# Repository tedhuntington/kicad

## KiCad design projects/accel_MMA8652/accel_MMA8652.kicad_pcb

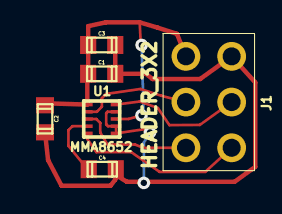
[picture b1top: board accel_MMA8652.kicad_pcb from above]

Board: 2 copper layers, 6 parts (0 on the bottom side), 7 nets.

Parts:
C1: 1uF; TED_SM0603
C2, C3, C4: .1uF; TED_SM0603
J1: HEADER_3X2; TED_HEADER_3x2_BOTTOM
U1: MMA8652; TED_DFN-10

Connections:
+2.8v: C1.1, C2.1, C3.1, J1.1, U1.1, U1.8
GND: C1.2, C2.2, C3.2, C4.2, J1.6, U1.6, U1.7, U1.9
INT1: J1.3, U1.3
INT2: J1.4, U1.5
unnamed: C4.1, U1.4
SCL: J1.2, U1.2
SDA: J1.5, U1.10

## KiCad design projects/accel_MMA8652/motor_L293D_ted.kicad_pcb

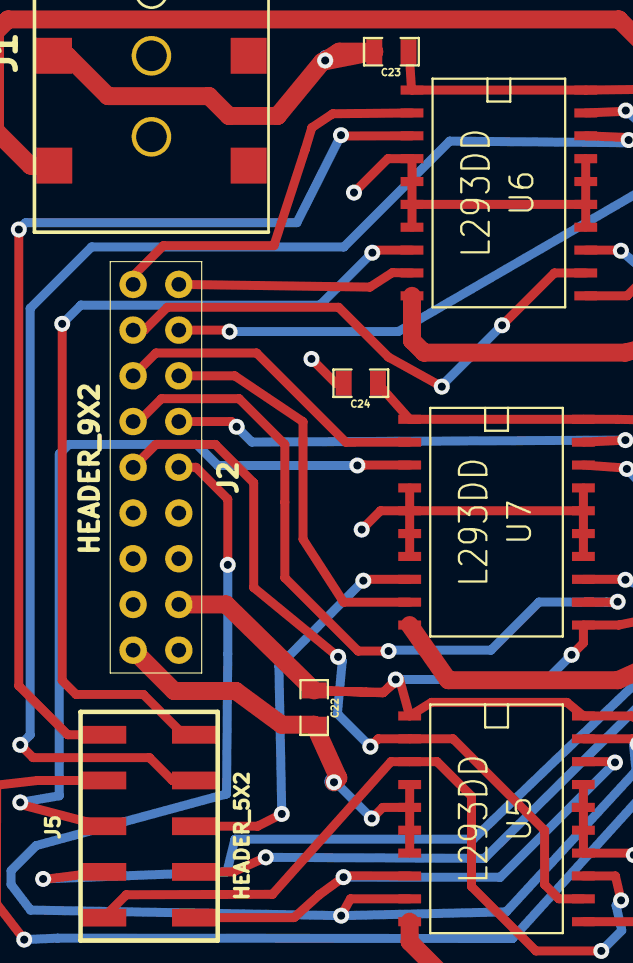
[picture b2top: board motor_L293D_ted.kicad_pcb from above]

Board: 2 copper layers, 9 parts (0 on the bottom side), 23 nets.

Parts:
C22, C23, C24: .1uF; TED_SM0805
J1: Motor DC_2.1MM; TED_DC_2.1mm_SMT
J2: HEADER_9X2; TED_HEADER_9x2_TOP
J5: HEADER_5X2; TED_HEADER_5x2_SMT
U5, U6, U7: L293DD; SO20

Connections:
+5v_Vbus: C22.1, C23.1, C24.1, J2.11, U5.1, U5.11, U5.20, U6.1, U6.11, U6.20, U7.1, U7.11, U7.20
GND: C22.2, C23.2, C24.2, J1.2, J2.9, U5.4, U5.5, U5.6, U5.7, U5.14, U5.15, U5.16, U5.17, U6.4, U6.5, U6.6, U6.7, U6.14, U6.15, U6.16, U6.17, U7.4, U7.5, U7.6, U7.7, U7.14, U7.15, U7.16, U7.17
ICSPCLK_M1-: J2.18, U6.9
ICSPDAT_M1+: J2.1, U6.2
M2+: J2.2, U6.12
M2-: J2.17, U6.19
M3+: J2.3, U7.2
M3-: J2.16, U7.9
M4+: J2.4, U7.12
M4-: J2.15, U7.19
M5+: J2.5, U5.2, U5.12
M5-: J2.14, U5.9, U5.19
Motor1+: J5.1, U6.3
Motor1-: J5.10, U6.8
Motor2+: J5.2, U6.13
Motor2-: J5.9, U6.18
Motor3+: J5.3, U7.3
Motor3-: J5.8, U7.8
Motor4+: J5.4, U7.13
Motor4-: J5.7, U7.18
Motor5+: J5.5, U5.3, U5.13
Motor5-: J5.6, U5.8, U5.18
Vin: J1.1, U5.10, U6.10, U7.10

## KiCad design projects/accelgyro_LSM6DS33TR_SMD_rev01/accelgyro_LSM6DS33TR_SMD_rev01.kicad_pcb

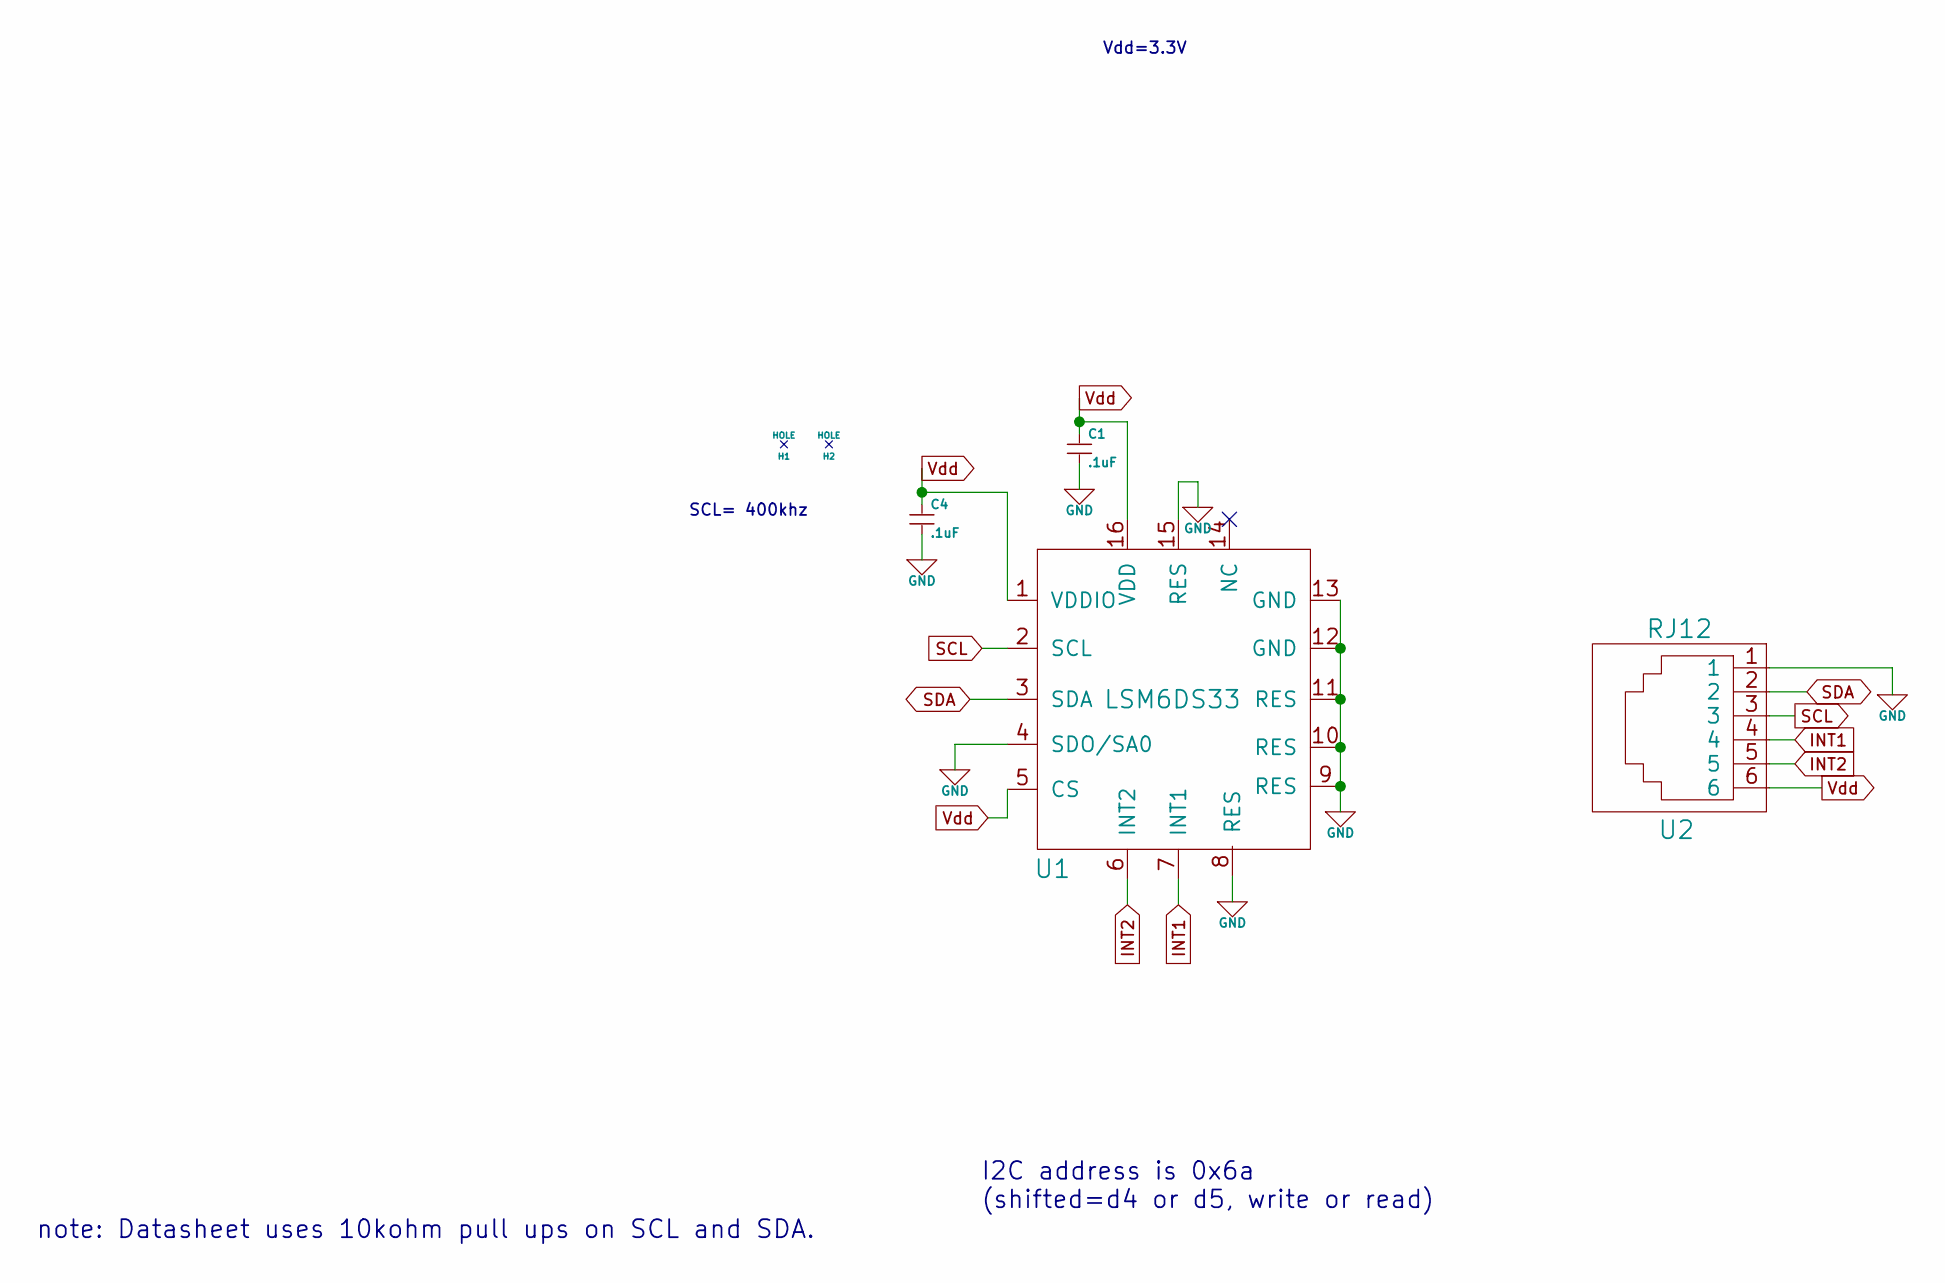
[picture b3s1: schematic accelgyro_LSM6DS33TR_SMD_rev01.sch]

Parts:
C1, C4: .1uF; TED_SM0603_C
H1, H2: HOLE; TED_Hole_3mm
U1: LSM6DS33; LGA-16
U2: RJ12; TED_RJ12_855135002

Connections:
GND: C1.2, C4.2, U1.4 (SDO/SA0), U1.8 (RES), U1.9 (RES), U1.10 (RES), U1.11 (RES), U1.12 (GND), U1.13 (GND), U1.15 (RES), U2.1
INT1: U1.7 (INT1), U2.4
INT2: U1.6 (INT2), U2.5
SCL: U1.2 (SCL), U2.3
SDA: U1.3 (SDA), U2.2
Vdd: C1.1, C4.1, U1.1 (VDDIO), U1.5 (CS), U1.16 (VDD), U2.6

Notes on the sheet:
Vdd=3.3V
I2C address is 0x6a (shifted=d4 or d5, write or read)
SCL= 400khz
note: Datasheet uses 10kohm pull ups on SCL and SDA.

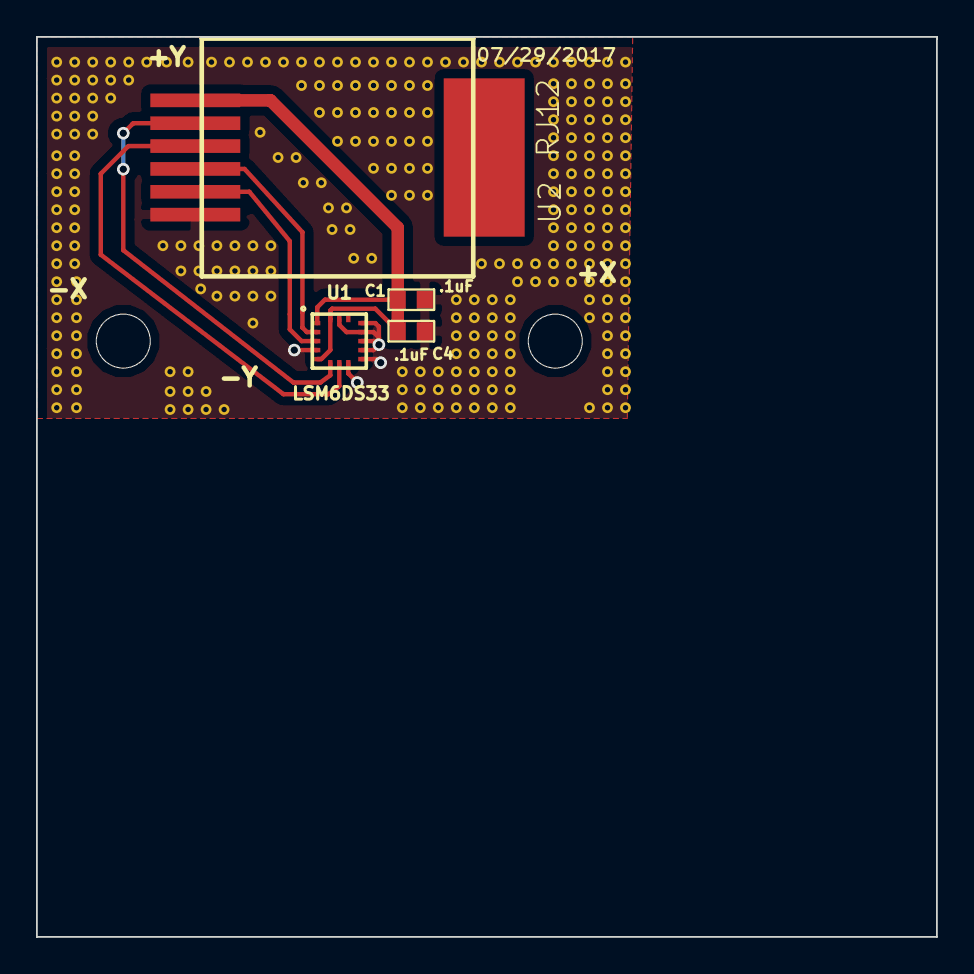
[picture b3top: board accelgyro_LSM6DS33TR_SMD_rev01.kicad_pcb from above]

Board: 2 copper layers, 50.0 x 50.0 mm, 6 parts (0 on the bottom side), 6 nets.

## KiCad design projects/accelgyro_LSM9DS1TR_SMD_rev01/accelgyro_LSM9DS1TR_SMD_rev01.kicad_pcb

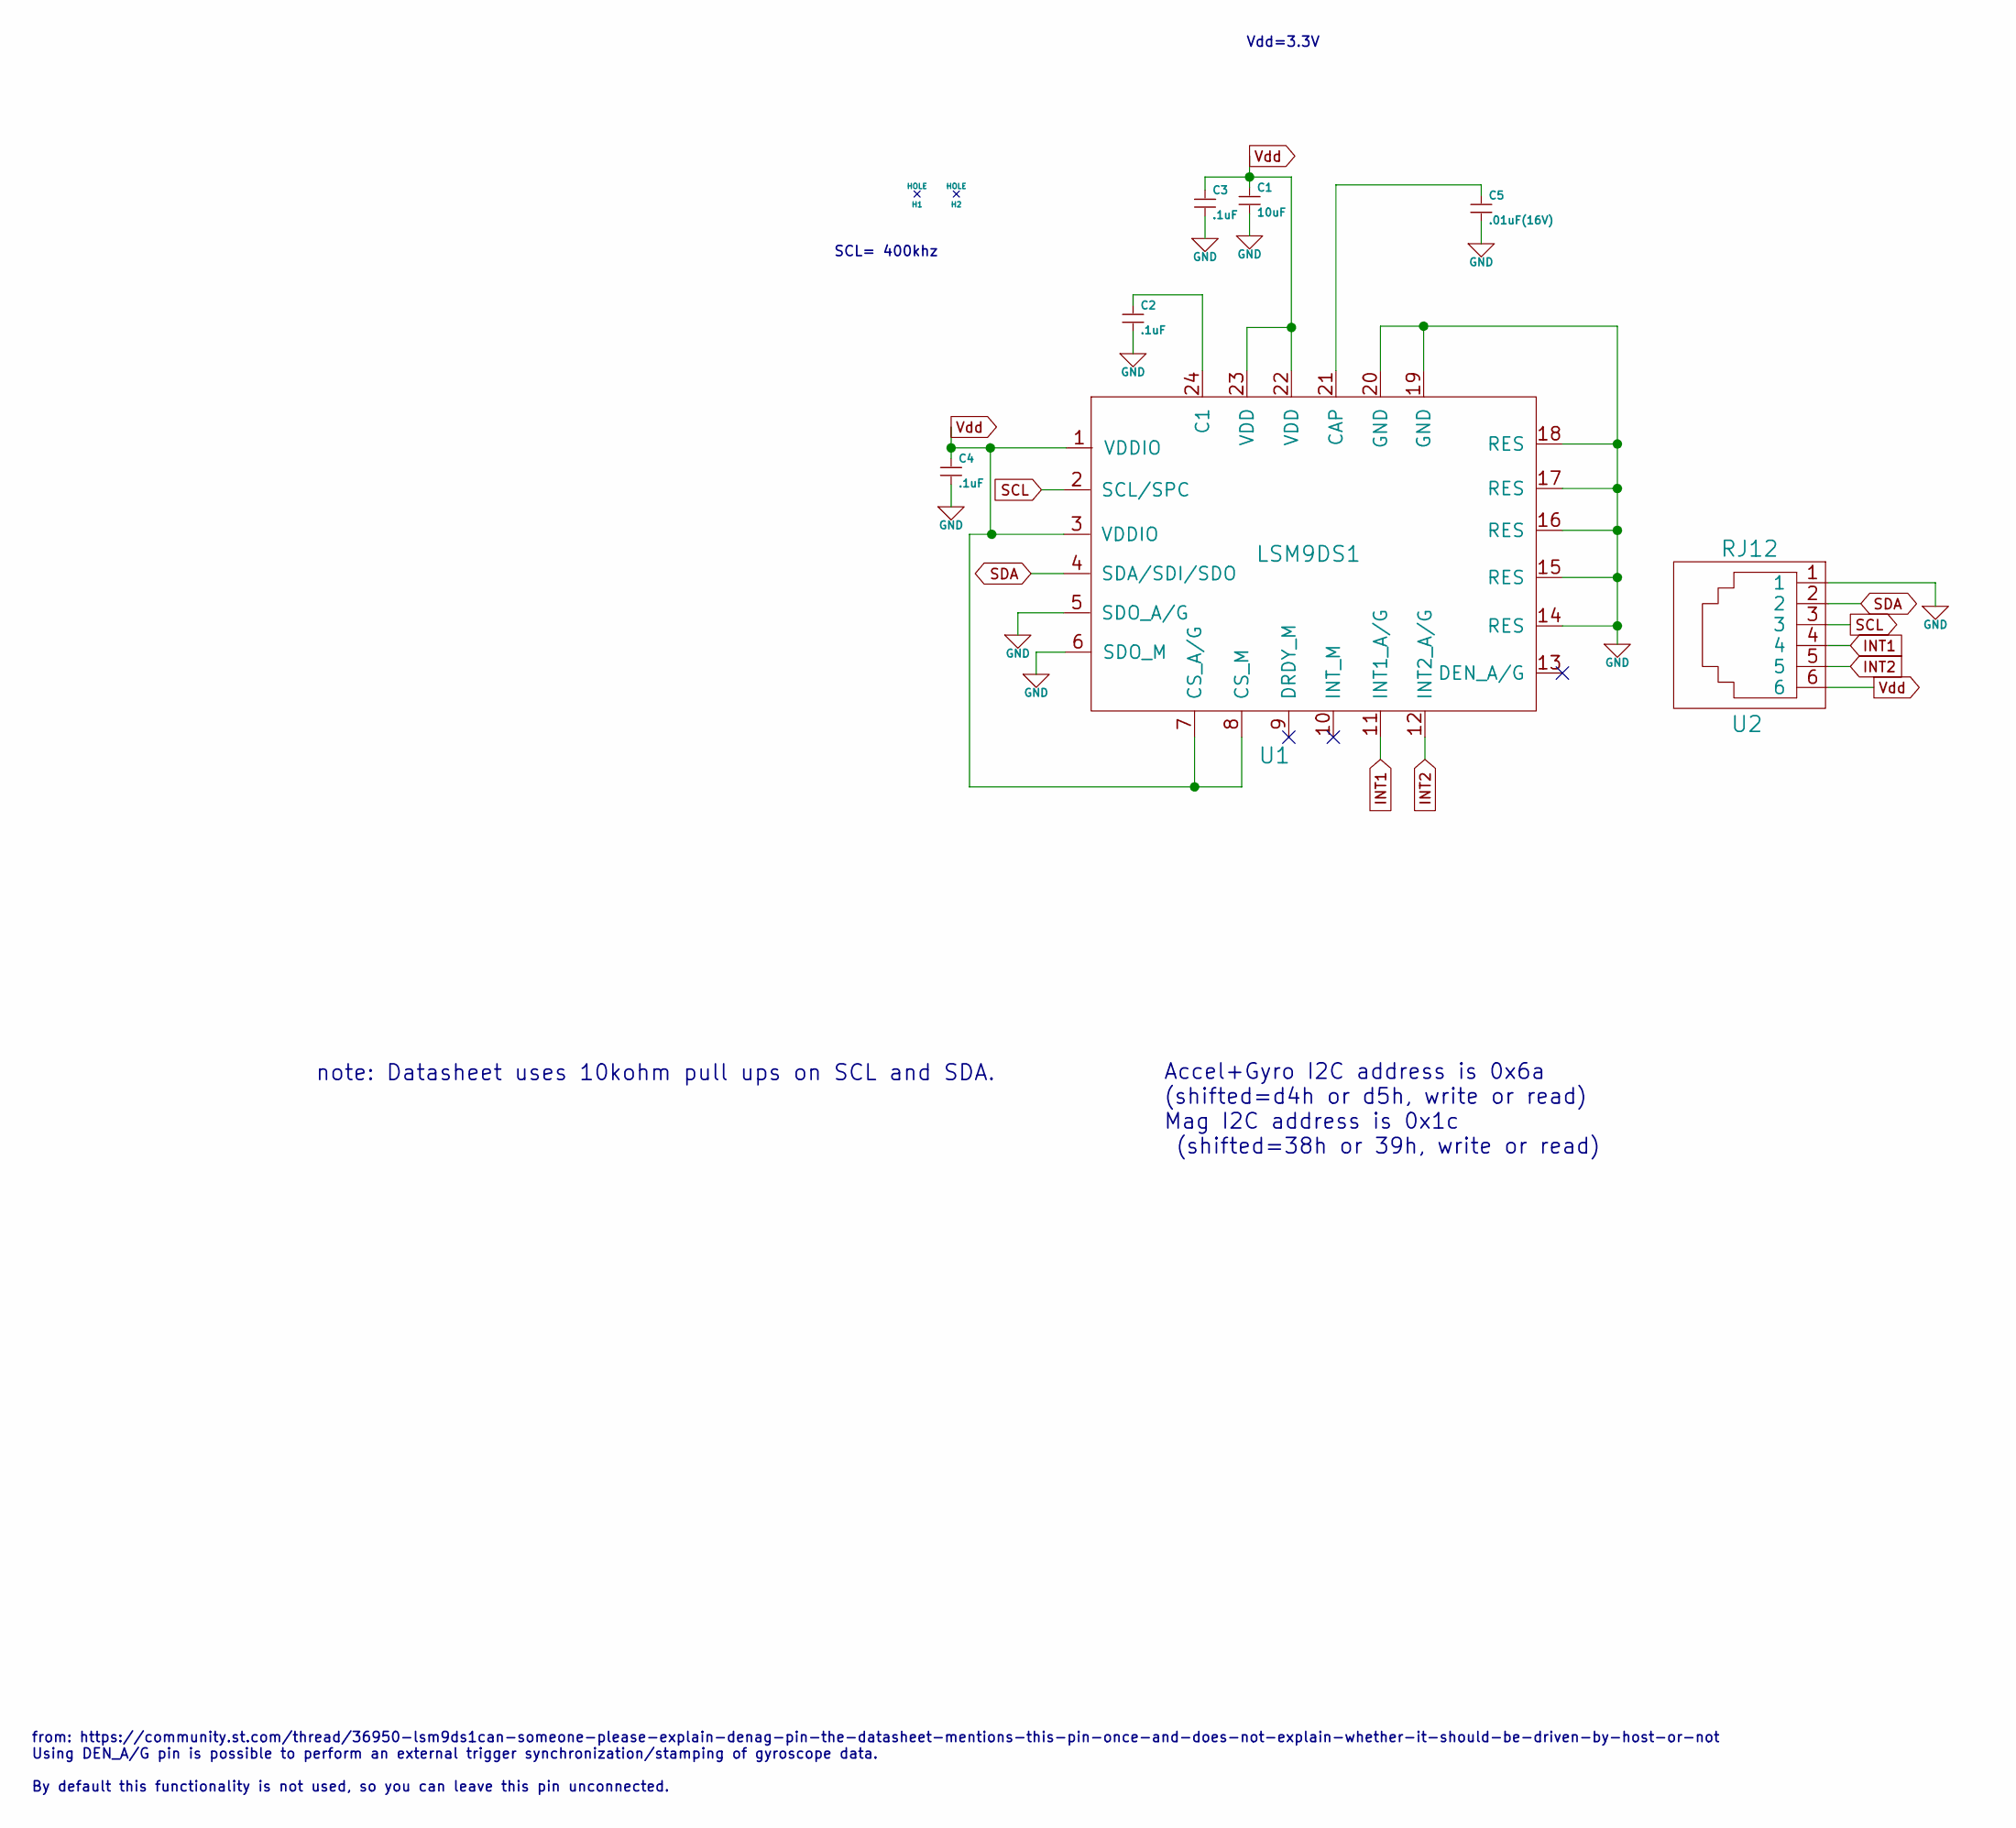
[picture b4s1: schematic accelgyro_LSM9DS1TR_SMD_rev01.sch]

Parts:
C1: 10uF; TED_SM0603_C
C2, C3, C4: .1uF; TED_SM0603_C
C5: .01uF(16V); TED_SM0603_C
H1, H2: HOLE; TED_Hole_3mm
U1: LSM9DS1; LGA-24
U2: RJ12; TED_RJ12_855135002

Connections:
GND: C1.2, C2.2, C3.2, C4.2, C5.2, U1.5 (SDO_A/G), U1.6 (SDO_M), U1.14 (RES), U1.15 (RES), U1.16 (RES), U1.17 (RES), U1.18 (RES), U1.19 (GND), U1.20 (GND), U2.1
INT1: U1.11 (INT1_A/G), U2.4
INT2: U1.12 (INT2_A/G), U2.5
unnamed: C2.1, U1.24 (C1)
unnamed: C5.1, U1.21 (CAP)
SCL: U1.2 (SCL/SPC), U2.3
SDA: U1.4 (SDA/SDI/SDO), U2.2
Vdd: C1.1, C3.1, C4.1, U1.1 (VDDIO), U1.3 (VDDIO), U1.7 (CS_A/G), U1.8 (CS_M), U1.22 (VDD), U1.23 (VDD), U2.6

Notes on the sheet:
Vdd=3.3V
Accel+Gyro I2C address is 0x6a (shifted=d4h or d5h, write or read) Mag I2C address is 0x1c (shifted=38h or 39h, write or read)
SCL= 400khz
note: Datasheet uses 10kohm pull ups on SCL and SDA.
from: https://community.st.com/thread/36950-lsm9ds1can-someone-please-explain-denag-pin-the-datasheet-mentions-this-pin-once-and-does-not-explain-whether-it-should-be-driven-by-host-or-not Using DEN_A/G pin is possible to perform an external trigger synchronization/stamping of gyroscope data. By de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

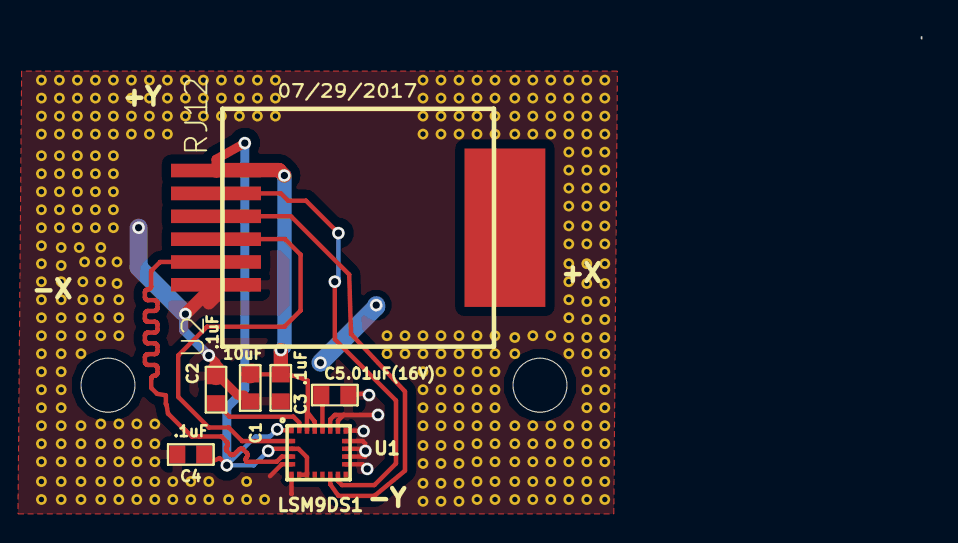
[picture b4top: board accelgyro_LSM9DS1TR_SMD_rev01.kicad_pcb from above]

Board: 2 copper layers, 9 parts (0 on the bottom side), 8 nets.

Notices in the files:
projects/accelgyro_LSM6DS33TR_SMD_rev01/accelgyro_LSM6DS33TR_SMD_rev01.kicad_pcb:
GPL License
